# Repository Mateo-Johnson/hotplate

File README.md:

# Reflow Hot Plate Controller
A custom controller board that turns a cheap aluminum hot plate and heating element into a precision reflow soldering station with PID temperature control and different reflow profiles.

## Finalized Schematic:

## Finalized Layout:

## Finalized Render:

## Finalized Firmware:
A minimal firmware example demonstrating core functionality of the Reflow Hot Plate Controller is available. It initializes SPI thermocouple sensing, runs a basic PID loop to regulate temperature, and drives the MOC3021-triggered TRIAC to control the heating element. This code provides a working control loop at ~10 Hz and serves as a starting point for integrating the touchscreen UI, reflow profiles, and SD logging in later revisions.

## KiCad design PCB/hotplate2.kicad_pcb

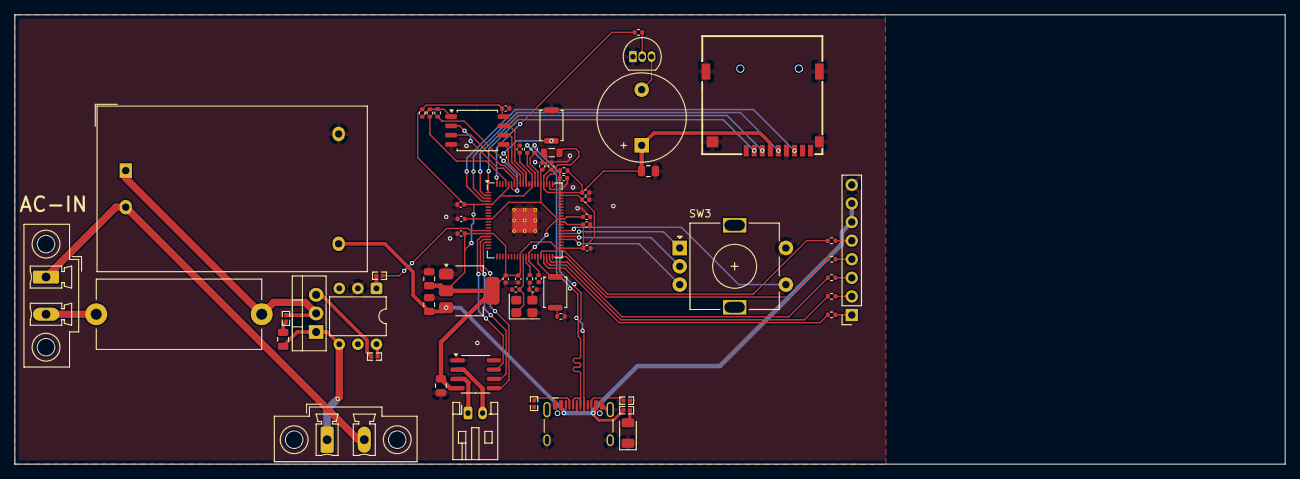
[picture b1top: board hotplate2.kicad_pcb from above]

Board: 2 copper layers, 173.5 x 61.4 mm, 66 parts (0 on the bottom side), 62 nets.

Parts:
BZ1: Buzzer; Buzzer_12x9.5RM7.6
C1, C2, C4, C5: 4.7u; C_0402_1005Metric
C3, C6, C7, C8, C9, C10, C11, C15, C16, C17, C19, C20: 100n; C_0402_1005Metric
C12, C13: 15p; C_0402_1005Metric
C14, C18, C21: 10u; C_0805_2012Metric
C22, C23: 100nF; C_0805_2012Metric
Card1: TF-115; TF-SMD_TF-115
D1: LTST-C150RKT; LED_1206_3216Metric
F1: Fuse; Fuseholder_Cylinder-5x20mm_Stelvio-Kontek_PTF78_Horizontal_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
J1: USB_C_Receptacle_USB2.0_16P; USB_C_Receptacle_HCTL_HC-TYPE-C-16P-01A
J2: Conn_01x02_Pin (Thermocouple); JST_PH_S2B-PH-K_1x02_P2.00mm_Horizontal
J4: Conn_01x08_Pin (TFT Connector); PinSocket_1x08_P2.54mm_Vertical
J5: Conn_01x02_Pin (Hot Plate Output); PhoenixContact_MCV_1,5_2-GF-5.08_1x02_P5.08mm_Vertical_Thre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
J9: Conn_01x02_Pin (AC Input); PhoenixContact_MCV_1,5_2-GF-5.08_1x02_P5.08mm_Vertical_Thre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
L1: 3.3u; L_0805_2012Metric
PS1: HLK-PM01; Converter_ACDC_Hi-Link_HLK-PMxx
Q1: 2N3904; TO-92_Inline
Q2: BTA16-600B; TO-220-3_Vertical
R1, R3, R12, R13, R17, R18, R19, R20, R21: 1k; R_0402_1005Metric
R2: 33; R_0402_1005Metric
R4, R5: RC0402FR-075K1L (5.1kΩ); R0402
R6: RC0402FR-13220RL (220Ω); R0402
R7, R8: 27; R_0402_1005Metric
R9, R11: DNF; R_0402_1005Metric
R10: 0; R_0402_1005Metric
R14, R15: 330Ω; R0402
R16: 100Ω; R0402
SW1, SW2: SKRKAGE020; SW_Push_SPST_NO_Alps_SKRK
SW3: RotaryEncoder_Switch; RotaryEncoder_Alps_EC11E-Switch_Vertical_H20mm
U1: RP2350_80QFN; QFN-80-1EP_10x10mm_P0.4mm_EP3.4x3.4mm_ThermalVias
U2: NCP1117-3.3_SOT223; SOT-223-3_TabPin2
U3: W25Q128JVS; SOIC-8_5.3x5.3mm_P1.27mm
U4: MOC3021M; DIP-6_W7.62mm
U5: MAX31855EASA; SOIC-8_3.9x4.9mm_P1.27mm
Y1: ABM8-272-T3; Crystal_SMD_3225-4Pin_3.2x2.5mm

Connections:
+1V1: C2.1, C3.1, C5.1, C6.1, L1.1, U1.10 (DVDD), U1.32 (DVDD), U1.51 (DVDD), U1.65 (VREG_FB)
+3V3: BZ1.1 (+), C1.1, C7.1, C8.1, C9.1, C10.1, C11.1, C15.1, C16.1, C17.1, C18.1, C19.1, C20.1, C21.1, C23.2, Card1.4 (VDD), R2.1, R11.1, U1.5 (IOVDD), U1.15 (IOVDD), U1.24 (IOVDD), U1.29 (IOVDD), U1.41 (IOVDD), U1.50 (IOVDD), U1.59 (ADC_AVDD), U1.60 (IOVDD), U1.64 (VREG_VIN), U1.68 (USB_OTP_VDD), U1.69 (QSPI_IOVDD), U1.76 (IOVDD), U2.2 (VO), U3.8 (VCC), U5.4 (V_{CC})
/01: R21.1, U1.36 (GPIO28)
/02: R20.1, U1.40 (GPIO32)
/03: R19.1, U1.39 (GPIO31)
/04: R18.1, U1.38 (GPIO30)
/05: R17.1, U1.37 (GPIO29)
/FLASH_SS: R9.2, R10.2, R11.2, U3.1 (~CS)
/GPIO0: R9.1, U1.77 (GPIO0)
/GPIO3: R13.2, U1.80 (GPIO3)
/GPIO4: Card1.2 (CD/DAT3), U1.1 (GPIO4)
/GPIO5: Card1.3 (CMD), U1.2 (GPIO5)
/GPIO6: Card1.5 (CLK), U1.3 (GPIO6)
/GPIO7: Card1.7 (DAT0), U1.4 (GPIO7)
/GPIO15: R14.1, U1.14 (GPIO15)
/GPIO16: U1.18 (GPIO18), U5.5 (SCK)
/GPIO17: U1.16 (GPIO16), U5.7 (SO)
/GPIO18: U1.17 (GPIO17), U5.6 (~CS)
/GPIO35: SW3.B, U1.44 (GPIO35)
/GPIO36: SW3.C, U1.45 (GPIO36)
/GPIO37: SW3.A, U1.46 (GPIO37)
/GPIO38: SW3.S1, U1.47 (GPIO38)
/QSPI_SCLK: U1.71 (QSPI_SCLK), U3.6 (CLK)
/QSPI_SD0: U1.72 (QSPI_SD0), U3.5 (DI(IO0))
/QSPI_SD1: U1.74 (QSPI_SD1), U3.2 (DO(IO1))
/QSPI_SD2: U1.73 (QSPI_SD2), U3.3 (IO2)
/QSPI_SD3: U1.70 (QSPI_SD3), U3.7 (IO3)
/QSPI_SS: R3.1, R10.1, U1.75 (QSPI_SS)
/RUN: SW2.2, U1.35 (RUN)
/USB_D+: J1.A6 (D+), J1.B6 (D+), R7.1
/USB_D-: J1.A7 (D-), J1.B7 (D-), R8.1
/VREG_AVDD: C4.1, R2.2, U1.61 (VREG_AVDD)
/VREG_LX: L1.2, U1.63 (VREG_LX)
/XIN: C12.1, U1.30 (XIN), Y1.1
/XOUT: R12.1, U1.31 (XOUT)
/~USB_BOOT: R3.2, SW1.1
AC: F1.1, PS1.1 (AC/L), Q2.2 (A2), R16.1
GND: C1.2, C2.2, C3.2, C4.2, C5.2, C6.2, C7.2, C8.2, C9.2, C10.2, C11.2, C12.2, C13.2, C14.2, C15.2, C16.2, C17.2, C18.2, C19.2, C20.2, C21.2, C23.1, Card1.6 (VSS), Card1.10 (SHELL), Card1.11 (SHELL), Card1.12 (SHELL), Card1.13 (SHELL), D1.1 (K), J1.A1 (GND), J1.A12 (GND), J1.B1 (GND), J1.B12 (GND), J1.S1 (SHIELD), J4.8, PS1.3 (-Vout), Q1.1 (E), R1.2, R4.2, R5.2, SW1.2, SW3.S2, U1.62 (VREG_PGND), U1.81 (GND), U2.1 (GND), U3.4 (GND), U4.2, U5.1 (GND), Y1.2, Y1.4
NEUT: J5.2, J9.1, PS1.2 (AC/N)
unnamed: BZ1.2 (-), Q1.3 (C)
unnamed: C13.1, R12.2, Y1.3
unnamed: C22.1, R16.2
unnamed: D1.2 (A), R6.2
unnamed: J1.A5 (CC1), R4.1
unnamed: J1.B5 (CC2), R5.1
unnamed: J2.1, U5.3 (T+)
unnamed: J2.2, U5.2 (T-)
unnamed: J4.1, R17.2
unnamed: J4.2, R18.2
unnamed: J4.3, R19.2
unnamed: J4.4, R20.2
unnamed: J4.5, R21.2
unnamed: C22.2, J5.1, Q2.1 (A1), U4.4
unnamed: F1.2, J9.2
unnamed: Q1.2 (B), R13.1
unnamed: Q2.3 (G), R15.2
unnamed: R1.1, SW2.1
unnamed: R14.2, U4.1
unnamed: R15.1, U4.6
unnamed: R8.2, U1.66 (USB_DM)
unnamed: R7.2, U1.67 (USB_DP)
VBUS: C14.1, J1.A4 (VBUS), J1.A9 (VBUS), J1.B4 (VBUS), J1.B9 (VBUS), J4.6, J4.7, PS1.4 (+Vout), R6.1, U2.3 (VI)

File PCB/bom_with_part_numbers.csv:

Reference,Qty,Value,DNP,Exclude from BOM,Exclude from Board,Footprint,Datasheet,Part Number
BZ1,1,Buzzer,,,,Buzzer_Beeper:Buzzer_12x9.5RM7.6,~,
"C1,C2,C4,C5",4,4.7u,,,,Capacitor_SMD:C_0402_1005Metric,~,
"C3,C6,C7,C8,C9,C10,C11,C15,C16,C17,C19,C20",12,100n,,,,Capacitor_SMD:C_0402_1005Metric,~,
"C12,C13",2,15p,,,,Capacitor_SMD:C_0402_1005Metric,~,
"C14,C18,C21",3,10u,,,,Capacitor_SMD:C_0805_2012Metric,~,
"C22,C23",2,100nF,,,,Capacitor_SMD:C_0805_2012Metric,~,
Card1,1,TF-115,,,,SDCARD:TF-SMD_TF-115,,TF-115
D1,1,LTST-C150RKT,,,,LED_SMD:LED_1206_3216Metric,~,LTST-C150RKT
F1,1,Fuse,,,,Fuse:Fuseholder_Cylinder-5x20mm_Stelvio-Kontek_PTF78_Horizontal_Open,~,
J1,1,USB_C_Receptacle_USB2.0_16P,,,,Connector_USB:USB_C_Receptacle_HCTL_HC-TYPE-C-16P-01A,,HC-TYPE-C-16P-01A
J2,1,Conn_01x02_Pin (Thermocouple),,,,Connector_JST:JST_PH_S2B-PH-K_1x02_P2.00mm_Horizontal,~,S2B-PH-K
J4,1,Conn_01x08_Pin (TFT Connector),,,,Connector_PinSocket_2.54mm:PinSocket_1x08_P2.54mm_Vertical,~,
J5,1,Conn_01x02_Pin (Hot Plate Output),,,,"Connector_Phoenix_MC_HighVoltage:PhoenixContact_MCV_1,5_2-GF-5.08_1x02_P5.08mm_Vertical_ThreadedFlange_MountHole",~,"MCV 1,5/2-GF-5.08"
J9,1,Conn_01x02_Pin (AC Input),,,,"Connector_Phoenix_MC_HighVoltage:PhoenixContact_MCV_1,5_2-GF-5.08_1x02_P5.08mm_Vertical_ThreadedFlange_MountHole",~,"MCV 1,5/2-GF-5.08"
L1,1,3.3u,,,,Inductor_SMD:L_0805_2012Metric,~,
PS1,1,HLK-PM01,,,,Converter_ACDC:Converter_ACDC_Hi-Link_HLK-PMxx,,HLK-PM01
Q1,1,2N3904,,,,Package_TO_SOT_THT:TO-92_Inline,,2N3904
Q2,1,BTA16-600B,,,,Package_TO_SOT_THT:TO-220-3_Vertical,,BTA16-600B
"R1,R3,R12,R13,R17,R18,R19,R20,R21",9,1k,,,,Resistor_SMD:R_0402_1005Metric,~,
R2,1,33,,,,Resistor_SMD:R_0402_1005Metric,~,
"R4,R5",2,RC0402FR-075K1L (5.1kΩ),,,,0402:R0402,~,RC0402FR-075K1L
R6,1,RC0402FR-13220RL (220Ω),,,,0402:R0402,~,RC0402FR-13220RL
"R7,R8",2,27,,,,Resistor_SMD:R_0402_1005Metric,~,
"R9,R11",2,DNF,,,,Resistor_SMD:R_0402_1005Metric,~,
R10,1,0,,,,Resistor_SMD:R_0402_1005Metric,~,
"R14,R15",2,330Ω,,,,0402:R0402,~,
R16,1,100Ω,,,,0402:R0402,~,
"SW1,SW2",2,SKRKAGE020,,,,Button_Switch_SMD:SW_Push_SPST_NO_Alps_SKRK,~,SKRKAGE020
SW3,1,RotaryEncoder_Switch,,,,Rotary_Encoder:RotaryEncoder_Alps_EC11E-Switch_Vertical_H20mm,~,EC11E
U1,1,RP2350_80QFN,,,,Package_DFN_QFN:QFN-80-1EP_10x10mm_P0.4mm_EP3.4x3.4mm_ThermalVias,,RP2350
U2,1,NCP1117-3.3_SOT223,,,,Package_TO_SOT_SMD:SOT-223-3_TabPin2,,NCP1117-3.3
U3,1,W25Q128JVS,,,,Package_SO:SOIC-8_5.3x5.3mm_P1.27mm,,W25Q128JVS
U4,1,MOC3021M,,,,Package_DIP:DIP-6_W7.62mm,,MOC3021M
U5,1,MAX31855EASA,,,,Package_SO:SOIC-8_3.9x4.9mm_P1.27mm,,MAX31855EASA
Y1,1,ABM8-272-T3,,,,Crystal:Crystal_SMD_3225-4Pin_3.2x2.5mm,~,ABM8-272-T3

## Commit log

2025-12-08 Initialize README with project title
2025-12-08 Revise README with project details and images
    Updated project title and added detailed descriptions and images for the finalized schematic, layout, and render.
2025-12-09 Add firmware example for Reflow Hot Plate Controller
    Added a minimal firmware example for the Reflow Hot Plate Controller, detailing its core functionality including SPI thermocouple sensing and PID loop operation.
2025-12-09 Rename firmware.c to firmware.c
